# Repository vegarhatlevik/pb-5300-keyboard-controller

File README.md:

# pb-5300-keyboard-controller
A controller to connect a keyboard for the Apple Powerbook 5300 to a USB based computer.

The purpose of this project is to enable the reuse of the keyboard in a Powerbook 5300 laptop without the logic board. Specifically, it provides a controller with a USB HID interface that enables connecting it to modern computers.

## Hardware
The project hardware consists of a PCB that is hosting an Arduino Leonardo capable microcontroller board. The board used in the development of this project is the Sparkfun Pro Micro. That board was chosen because it was readily at hand in the component cupboard, but in hindsight it might have been better to go with a microcontroller with a higher number of I/O pins. That would have reduced the need for external chips like the demuxers and the shift registers. An idea for a future improvement would be to reimplement it using a larger PIC microcontroller.

## Firmware
The firmware implements a basic keyboard matrix scan and uses a library for USB HID functionality. The Atmel32u4 microcontroller used in Leonardo class boards has built in USB functionality. The library just makes it easier to deal with USB HID, without getting into the details of USB HID protocols. The choice fell on [NicoHood's HID libary](https://github.com/NicoHood/HID). It is very similar to the built in Keyboard of Arduino development tools, and it was chosen over the Arduino library for the simple reason that it provides handling of a keyboard's LED status without diving deep. An added bonus of the chosen library is that it supports the HID boot protocol, which may help with some BIOS implementations, but it is not the reason why it was chosen.

## Credits

During this project I relied heavily on the [excellent post about keyboard design by Michal Trybus](http://blog.komar.be/how-to-make-a-keyboard-the-matrix/) and I stole the idea of using shift registers for working around limited I/O pin numbers from [mehmedbasic.dk](https://mehmedbasic.dk/post/74hc595-keyboard/).

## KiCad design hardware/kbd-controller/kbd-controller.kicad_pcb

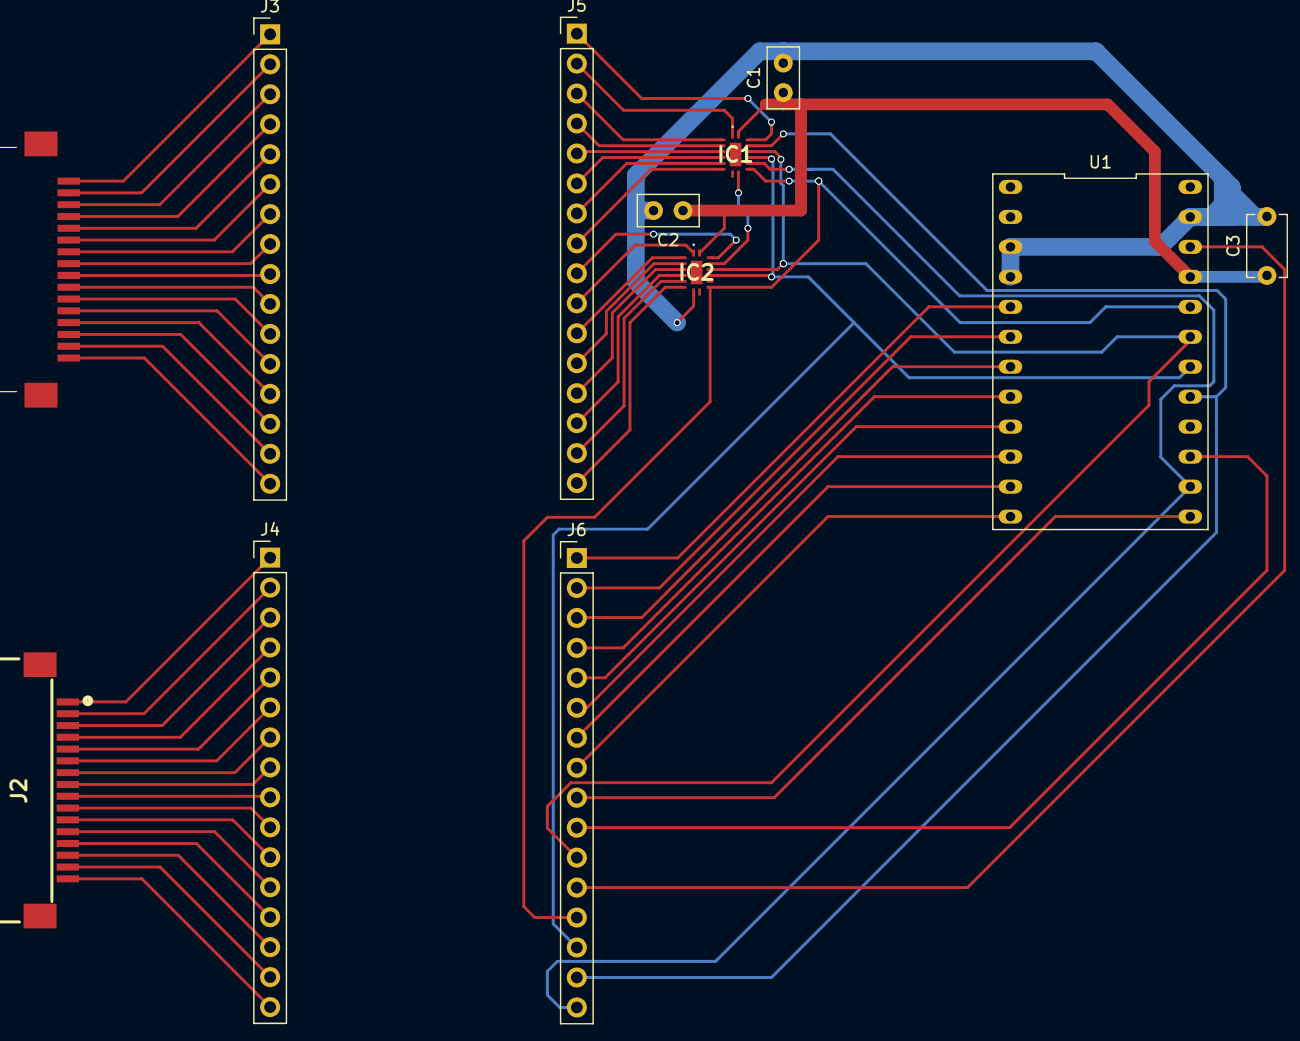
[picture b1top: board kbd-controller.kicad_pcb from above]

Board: 2 copper layers, 12 parts (0 on the bottom side), 67 nets.

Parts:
C1, C2: C_Small; C_Disc_D5.0mm_W2.5mm_P2.50mm
C3: C_Polarized_Small; C_Disc_D5.1mm_W3.2mm_P5.00mm
IC1, IC2: SN74AC596BQBR
J1: 52207-1633 MOLEX - Conector FFC/FPC; 52207-1633 MOLEX - Conector FFC_FPC
J2: 52271-1679 MOLEX - Conector FFC/FPC; 52271-1679 MOLEX - Conector FFC_FPC
J3, J4, J5, J6: Conn_01x16_Socket; PinHeader_1x16_P2.54mm_Vertical
U1: Pro Micro Leonardo

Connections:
C1: IC1.15 (QA), J5.1
C2: IC1.1 (QB), J5.2
C3: IC1.2 (QC), J5.3
C4: IC1.3 (QD), J5.4
C5: IC1.4 (QE), J5.5
C6: IC1.5 (QF), J5.6
C7: IC1.6 (QG), J5.7
C8: IC1.7 (QH), J5.8
C9: IC2.15 (QA), J5.9
C10: IC2.1 (QB), J5.10
C11: IC2.2 (QC), J5.11
C12: IC2.3 (QD), J5.12
C13: IC2.4 (QE), J5.13
C14: IC2.5 (QF), J5.14
C15: IC2.6 (QG), J5.15
C16: IC2.7 (QH), J5.16
D10: J6.9, U1.13 (A10/D10)
D14: J6.10, U1.15 (D14)
GND: C1.2, C2.2, C3.2, IC1.8 (GND), IC2.8 (GND), U1.3 (GND), U1.4 (GND), U1.23 (GND)
unnamed: IC1.9 (QH'), IC2.14 (SER)
unnamed: J1.1, J3.1
unnamed: J1.2, J3.2
unnamed: J1.3, J3.3
unnamed: J1.4, J3.4
unnamed: J1.5, J3.5
unnamed: J1.6, J3.6
unnamed: J1.7, J3.7
unnamed: J1.8, J3.8
unnamed: J1.9, J3.9
unnamed: J1.10, J3.10
unnamed: J1.11, J3.11
unnamed: J1.12, J3.12
unnamed: J1.13, J3.13
unnamed: J1.14, J3.14
unnamed: J1.15, J3.15
unnamed: J1.16, J3.16
unnamed: J2.1, J4.1
unnamed: J2.2, J4.2
unnamed: J2.3, J4.3
unnamed: J2.4, J4.4
unnamed: J2.5, J4.5
unnamed: J2.6, J4.6
unnamed: J2.7, J4.7
unnamed: J2.8, J4.8
unnamed: J2.9, J4.9
unnamed: J2.10, J4.10
unnamed: J2.11, J4.11
unnamed: J2.12, J4.12
unnamed: J2.13, J4.13
unnamed: J2.14, J4.14
unnamed: J2.15, J4.15
unnamed: J2.16, J4.16
R1: J6.1, U1.5 (D2)
R2: J6.2, U1.6 (D3)
R3: J6.3, U1.7 (D4/A6)
R4: J6.4, U1.8 (D5)
R5: J6.5, U1.9 (D6/A7)
R6: J6.6, U1.10 (D7)
R7: J6.7, U1.11 (D8/A8)
R8: J6.8, U1.12 (D9/A9)
RCLK: IC1.12 (RCLK), IC2.12 (RCLK), J6.14, U1.18 (A1/D19)
RST: J6.12, U1.22 (RST)
SER: IC1.14 (SER), J6.15, U1.17 (A0/D18)
SRCLK: IC1.11 (SRCLK), IC2.11 (SRCLK), J6.16, U1.14 (D16)
VCC: C1.1, C2.1, C3.1, IC1.16 (VCC), IC2.16 (VCC), U1.21 (VCC)
/OE: IC1.13 (~OE), IC2.13 (~OE), J6.11, U1.19 (A2/D20)
/SRCLR: IC1.10 (~SRCLR), IC2.10 (~SRCLR), J6.13, U1.20 (A3/D21)

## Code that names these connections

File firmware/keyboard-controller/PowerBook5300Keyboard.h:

class PowerBook5300Keyboard {
private:

  /////////////////////////////////////////////////////////////////////////////
  // Key definitions

  static const uint8_t KEY_PWR = 0xFF; // This should be handled specially, but not yet sure how.
  static const uint8_t KEY_NONE = 0; // Not really needed because it will never be detected.

  static const uint8_t KEY_X = 'x';
  static const uint8_t KEY_C = 'c';
  static const uint8_t KEY_Z = 'z';
  static const uint8_t KEY_V = 'v';
  static const uint8_t KEY_S = 's';
  static const uint8_t KEY_D = 'd';
  static const uint8_t KEY_A = 'a';
  static const uint8_t KEY_F = 'f';

  /////////////////////////////////////////////////////////////////////////////
  // Pin definitions

  static const uint8_t MAX_COLS = 4;
  static const uint8_t MAX_ROWS = 4;

  static const uint8_t ROW_1 = 2;
  static const uint8_t ROW_2 = 3;
  static const uint8_t ROW_3 = 4;
  static const uint8_t ROW_4 = 5;
  /*
  static const uint8_t ROW_5 = 6;
  static const uint8_t ROW_6 = 7;
  static const uint8_t ROW_7 = 8;
  static const uint8_t ROW_8 = 9;

  static const uint8_t _SRCLR = 21;
  static const uint8_t _OE = 20;
  static const uint8_t RCLK = 19;
  static const uint8_t SER = 18;
  static const uint8_t _DETECT = 14;
  static const uint8_t SRCLK = 16;
  */

  static const uint8_t _COL_2 = 6;
  static const uint8_t _COL_3 = 7;
  static const uint8_t _COL_4 = 8;
  static const uint8_t _COL_5 = 9;

  static const uint8_t _CLED = 15; // active low

  const uint8_t outputPins[5] = {_CLED, _COL_2, _COL_3, _COL_4, _COL_5};
  const uint8_t inputPullupPins[4] = {ROW_1, ROW_2, ROW_3, ROW_4};

  /////////////////////////////////////////////////////////////////////////////
  // Layout

  const uint8_t columns[MAX_COLS]={_COL_2, _COL_3, _COL_4, _COL_5};
  const uint8_t rows[MAX_ROWS]={ROW_1, ROW_2, ROW_3, ROW_4};

  uint8_t keyMatrix[MAX_ROWS][MAX_COLS];

  uint8_t previousMatrix[MAX_COLS][MAX_ROWS] = {{1}};
  uint8_t readMatrix[MAX_COLS][MAX_ROWS] = {{1}};

public:
  PowerBook5300Keyboard();
  void init();
  void scan();
};

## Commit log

2026-01-22 Ignore some more files
2026-01-22 Decoupling capacitors
2026-01-24 Update README.md
    Project renamed
2026-01-26 Proof of concept. Implemented just 4 columns and 4 rows due to I/O pin limitation. Will need to be expanded when hardware is complete with shift registers and line decoders.
2026-01-26 Switched to using HID Project library by Nico Hood instead of the standard Keyboard library from Arduino. Added support for Caps Lock led, which is the reason for switching library.
2026-02-08 Update README.md
    Minor grammar improvements.
